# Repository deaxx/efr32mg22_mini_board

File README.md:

# efr32mg22_mini_board
Not tested!

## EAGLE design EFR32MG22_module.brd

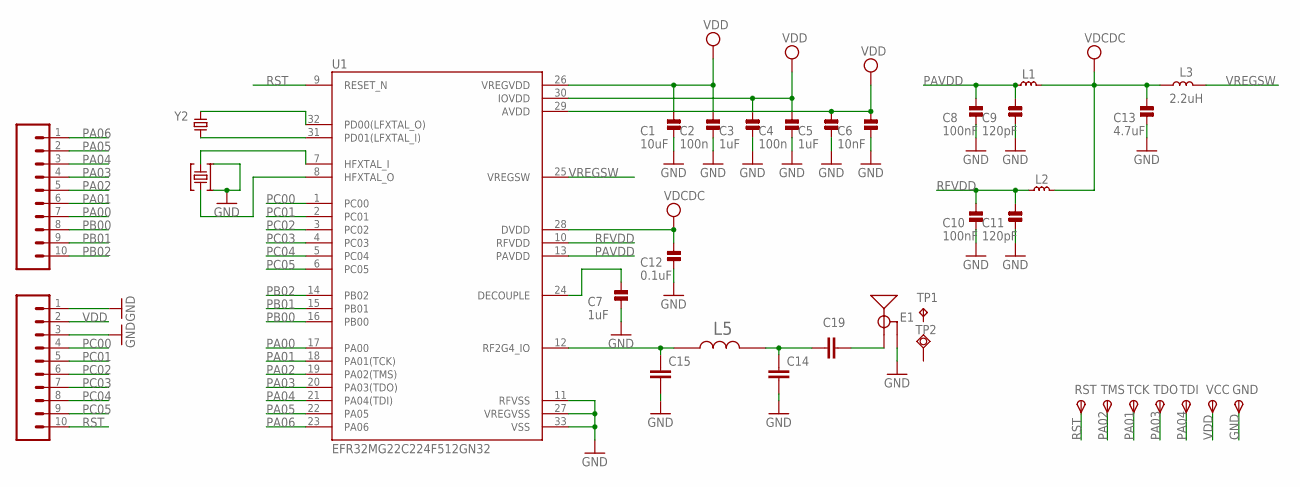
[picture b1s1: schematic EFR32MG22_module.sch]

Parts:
C1: 10uF; _PKG_C_0805
C2, C4: 100n; _PKG_C_0402
C3, C5, C7: 1uF; _PKG_C_0402
C6: 10nF; _PKG_C_0402
C8, C10: 100nF; _PKG_C_0402
C9, C11: 120pF; _PKG_C_0402
C12: 0.1uF; _PKG_C_0402
C13: 4.7uF; _PKG_C_0402
C14: 1.3pF; CAPC1005X40N
C15: 1.2pF; CAPC1005X40N
C19: 18pF; CAPC1005X40N
E1: ANTENNA-GROUNDEDTRACE-15.2MM; TRACE_ANTENNA_2.4GHZ_15.2MM
GND: TPSTP11R; TP11R
J1, J2: CONN_061.27MM; 1X06_1.27MM
L1, L2: BLM18AG102SN1; _PKG_L_0603
L3: 2.2uH; INDC2520X120N
L5: 2.6nH; INDC1005X40N
RST: TPSTP11R; TP11R
TCK: TPSTP11R; TP11R
TDI: TPSTP11R; TP11R
TDO: TPSTP11R; TP11R
TMS: TPSTP11R; TP11R
TP1: TPTP06SQ; TP05SQ
TP2: TPSQTP15SQ; TP15SQ
U1: EFR32MG22C224F512GN32; QFN50P500X500X90-33N
VCC: TPSTP11R; TP11R
Y1: 38.4MHZ; XTAL-4P-2016
Y2: 32.768KHz; XTAL-2P-3215

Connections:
GND: C1.2, C2.2, C3.2, C4.2, C5.2, C6.2, C7.2, C8.2, C9.2, C10.2, C11.2, C12.2, C13.2, C14.2, C15.2, E1.GND, GND.TP, J2.1, J2.3, U1.11 (RFVSS), U1.27 (VREGVSS), U1.33 (VSS), Y1.2, Y1.4
unnamed: C15.1, L5.1, U1.12 (RF2G4_IO)
unnamed: C7.1, U1.24 (DECOUPLE)
unnamed: U1.7 (HFXTAL_I), Y1.3
unnamed: U1.31 (PD01(LFXTAL_I)), Y2.2
unnamed: U1.32 (PD00(LFXTAL_O)), Y2.1
unnamed: C14.1, C19.1, L5.2
unnamed: C19.2, E1.ANT (SIGNAL)
unnamed: U1.8 (HFXTAL_O), Y1.1
PA00: J1.7, U1.17 (PA00)
PA01: J1.6, TCK.TP, U1.18 (PA01(TCK))
PA02: J1.5, TMS.TP, U1.19 (PA02(TMS))
PA03: J1.4, TDO.TP, U1.20 (PA03(TDO))
PA04: J1.3, TDI.TP, U1.21 (PA04(TDI))
PA05: J1.2, U1.22 (PA05)
PA06: J1.1, U1.23 (PA06)
PAVDD: C8.1, C9.1, L1.1, U1.13 (PAVDD)
PB00: J1.8, U1.16 (PB00)
PB01: J1.9, U1.15 (PB01)
PB02: J1.10, U1.14 (PB02)
PC00: J2.4, U1.1 (PC00)
PC01: J2.5, U1.2 (PC01)
PC02: J2.6, U1.3 (PC02)
PC03: J2.7, U1.4 (PC03)
PC04: J2.8, U1.5 (PC04)
PC05: J2.9, U1.6 (PC05)
RFVDD: C10.1, C11.1, L2.1, U1.10 (RFVDD)
RST: J2.10, RST.TP, U1.9 (RESET_N)
VDD: C1.1, C2.1, C3.1, C4.1, C5.1, C6.1, J2.2, U1.26 (VREGVDD), U1.29 (AVDD), U1.30 (IOVDD), VCC.TP
VPP: C12.1, C13.1, L1.2, L2.2, L3.1, U1.28 (DVDD)
VREGSW: L3.2, U1.25 (VREGSW)

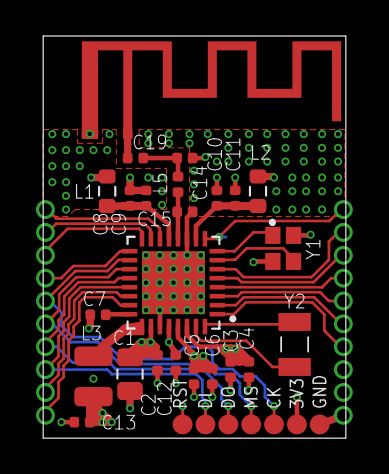
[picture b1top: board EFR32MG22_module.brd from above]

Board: 4 copper layers, 16.8 x 22.3 mm, 35 parts (0 on the bottom side), 31 nets.

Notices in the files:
parts and their libraries:
SparkFun-RF: Licensing: Creative Commons ShareAlike 4.0 International - https://creativecommons.org/licenses/by-sa/4.0
